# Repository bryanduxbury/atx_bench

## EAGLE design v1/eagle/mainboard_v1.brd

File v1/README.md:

# atx_bench

An digitally-adjustable bench power supply built around an ATX computer power supply.

Check out the DATASHEET for info on features.

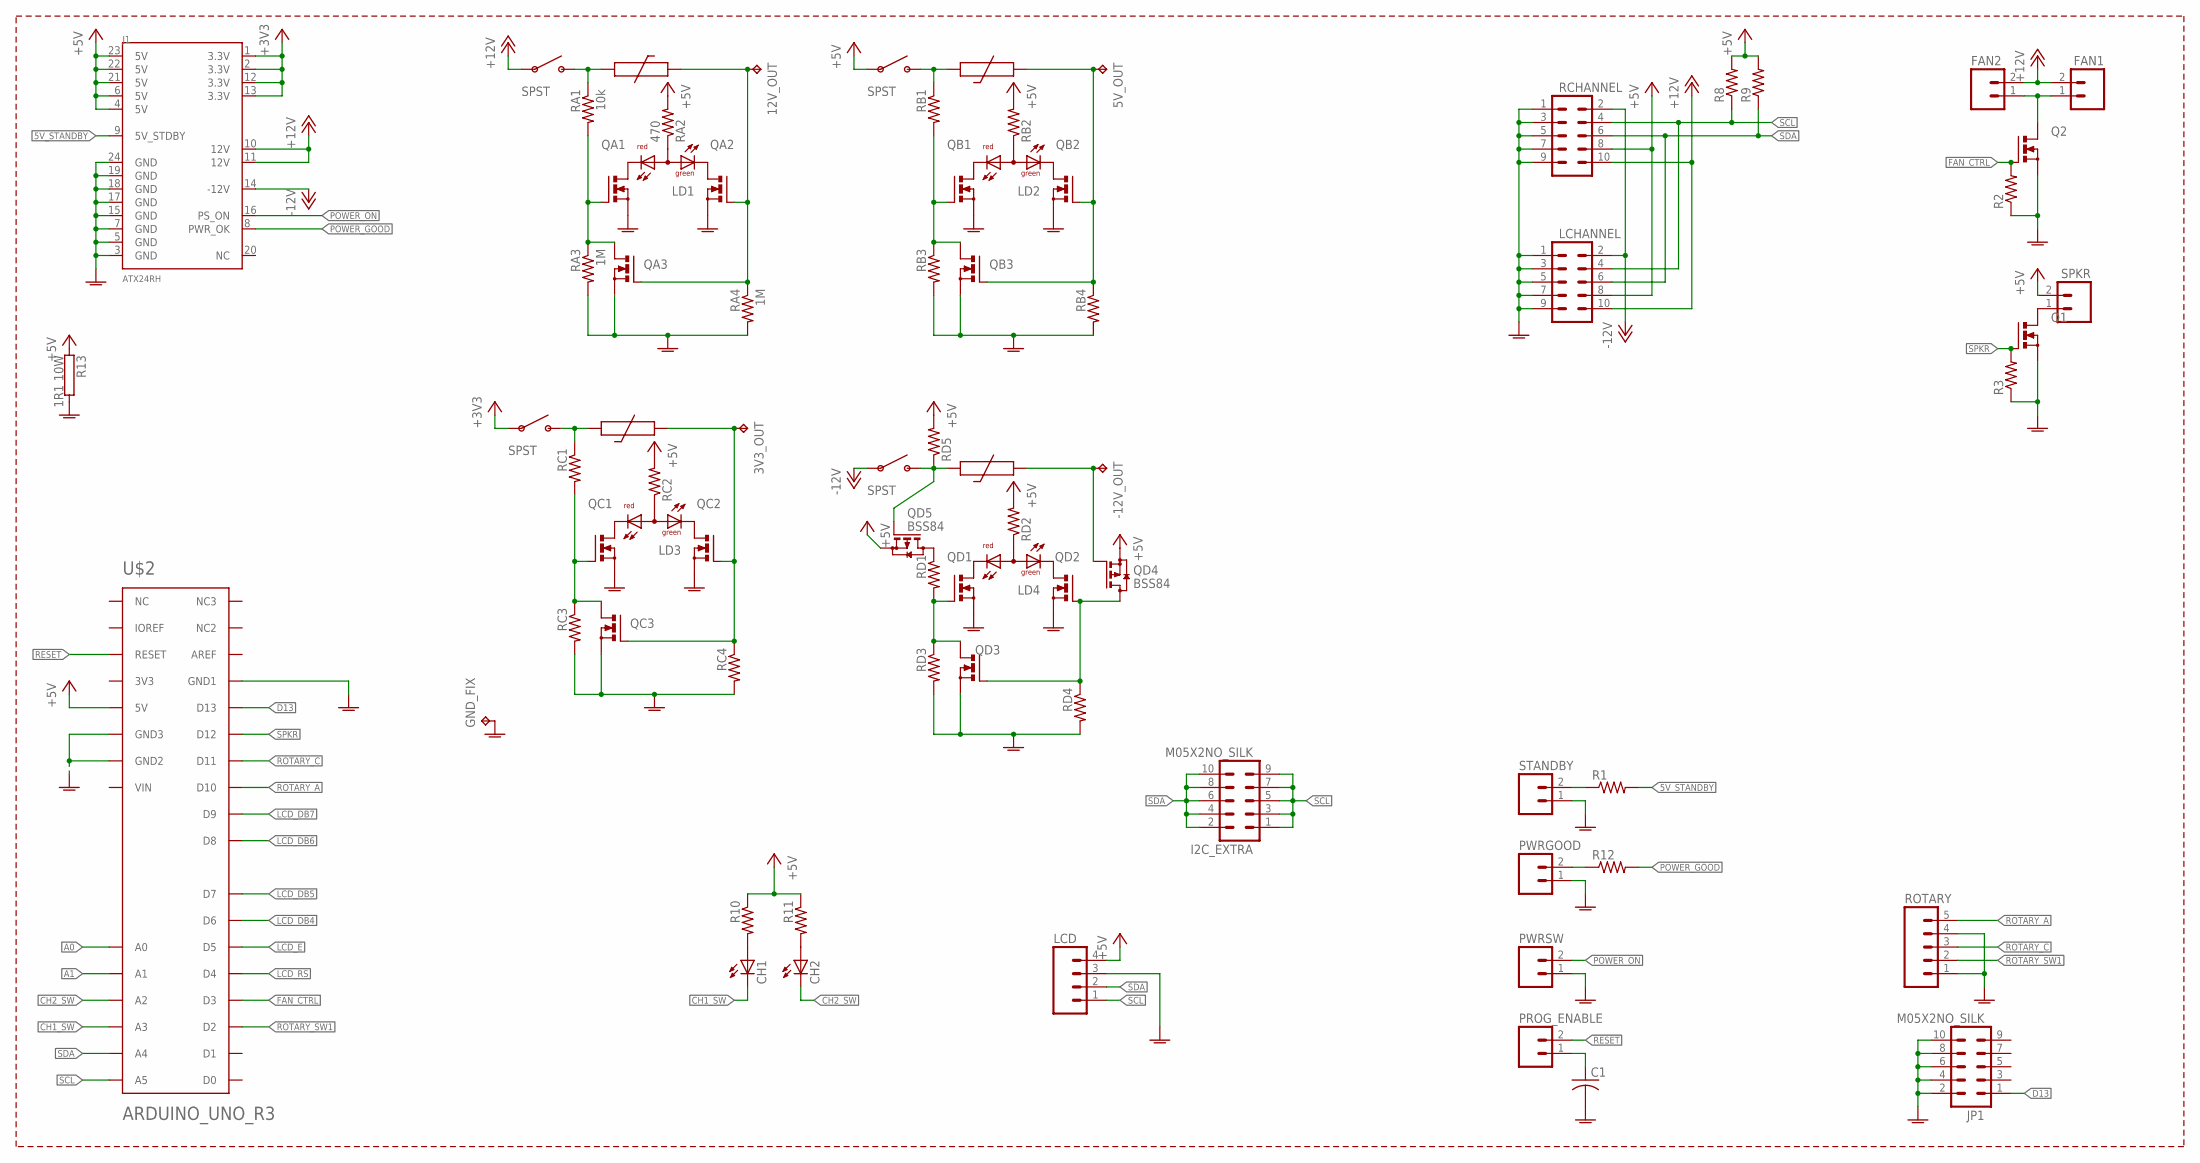
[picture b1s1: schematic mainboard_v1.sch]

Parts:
3V3_OUT, 5V_OUT, 12V_OUT: TPPAD1-20; P1-20
-12V_OUT: TPPAD1-20; P1-20
C1: C-USC0805; C0805
CH1, CH2: LED5MM
FAN1, FAN2: M02PTH; 1X02
GND_FIX: TPPAD1-20; P1-20
I2C_EXTRA: M05X2NO_SILK; 2X5_NOSILK
J1: ATX24RH; ATX24_RIGHT_ANGLE
JP1: M05X2NO_SILK; 2X5_NOSILK
LCD: M04; 04P
LCHANNEL: M05X2SHD; 2X5-SHROUDED
LD1, LD2, LD3, LD4: DUOLED-RG-A; DUOLED-A-5MM
PROG_ENABLE: M02PTH; 1X02
PWRGOOD: M02PTH; 1X02
PWRSW: M02PTH; 1X02
Q1, Q2: 2N7002L; SOT23
QA1, QA2, QA3: 2N7002L; SOT23
QB1, QB2, QB3: 2N7002L; SOT23
QC1, QC2, QC3: 2N7002L; SOT23
QD1, QD2, QD3: 2N7002L; SOT23
QD4, QD5: BSS84; SOT23
R1, R2, R3, R8, R9, R10, R11, R12: R-US_R0805; R0805
R13: 1R1 10W; MNS-5
RA1: 10k; R0805
RA2: 470; R0805
RA3, RA4: 1M; R0805
RB1, RB2, RB3, RB4: R-US_R0805; R0805
RC1, RC2, RC3, RC4: R-US_R0805; R0805
RCHANNEL: M05X2SHD; 2X5-SHROUDED
RD1, RD2, RD3, RD4, RD5: R-US_R0805; R0805
ROTARY: M05; 05P
SPKR: M02PTH; 1X02
STANDBY: M02PTH; 1X02
U$1, U$3, U$4, U$5: MF-R300; MR-300
U$2: ARDUINO_UNO_R3MINIMUM; ARDUINO_UNO_R3_MIN
U$6, U$8, U$9, U$10: SPST; 2P_REMOTE

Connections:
5V_OUT: 5V_OUT.TP, QB2.1 (G), QB3.1 (G), RB4.1, U$3.P$2 (2)
5V_OUT1: 3V3_OUT.TP, QC2.1 (G), QC3.1 (G), RC4.1, U$4.P$2 (2)
5V_STANDBY: J1.9 (5V_STDBY), R1.2
+3V3: J1.1 (3.3V), J1.2 (3.3V), J1.12 (3.3V), J1.13 (3.3V), U$9.1
+5V: J1.4 (5V), J1.6 (5V), J1.21 (5V), J1.22 (5V), J1.23 (5V), LCD.4, LCHANNEL.8, QD4.2 (S), QD5.2 (S), R8.2, R9.2, R10.1, R11.1, R13.1, RA2.2, RB2.2, RC2.2, RCHANNEL.8, RD2.2, RD5.2, SPKR.2, U$2.5V, U$8.1
+12V: FAN1.2, FAN2.2, J1.10 (12V), J1.11 (12V), LCHANNEL.10, RCHANNEL.10, U$6.1
-12V: J1.14 (-12V), LCHANNEL.2, RCHANNEL.2, U$10.1
A0: U$2.A0
A1: U$2.A1
CH1_SW: CH1.K (C), U$2.A3
CH2_SW: CH2.K (C), U$2.A2
D13: JP1.1, U$2.D13
FAN_CTRL: Q2.1 (G), R2.2, U$2.D3
GNDA: C1.2, GND_FIX.TP, J1.3 (GND), J1.5 (GND), J1.7 (GND), J1.15 (GND), J1.17 (GND), J1.18 (GND), J1.19 (GND), J1.24 (GND), JP1.2, JP1.4, JP1.6, JP1.8, JP1.10, LCD.3, LCHANNEL.1, LCHANNEL.3, LCHANNEL.5, LCHANNEL.7, LCHANNEL.9, PWRGOOD.1, PWRSW.1, Q1.2 (S), Q2.2 (S), QA1.2 (S), QA2.2 (S), QA3.2 (S), QB1.2 (S), QB2.2 (S), QB3.2 (S), QC1.2 (S), QC2.2 (S), QC3.2 (S), QD1.2 (S), QD2.2 (S), QD3.2 (S), R2.1, R3.1, R13.2, RA3.2, RA4.2, RB3.2, RB4.2, RC3.2, RC4.2, RCHANNEL.1, RCHANNEL.3, RCHANNEL.5, RCHANNEL.7, RCHANNEL.9, RD3.2, RD4.2, ROTARY.1, ROTARY.4, STANDBY.1, U$2.GND (GND1), U$2.GND2, U$2.GND3
LCD_DB4: U$2.D6
LCD_DB5: U$2.D7
LCD_DB6: U$2.D8
LCD_DB7: U$2.D9
LCD_E: U$2.D5
LCD_RS: U$2.D4
unnamed: FAN1.1, FAN2.1, Q2.3 (D)
unnamed: R1.1, STANDBY.2
unnamed: Q1.3 (D), SPKR.1
unnamed: CH1.A, R10.2
unnamed: CH2.A, R11.2
unnamed: LD2.A, RB2.1
unnamed: LD1.A, RA2.1
unnamed: LD1.CX (CG), QA2.3 (D)
unnamed: LD1.CR, QA1.3 (D)
unnamed: LD2.CX (CG), QB2.3 (D)
unnamed: LD2.CR, QB1.3 (D)
unnamed: PWRGOOD.2, R12.1
unnamed: C1.1, PROG_ENABLE.1
unnamed: RA1.1, U$1.P$2 (2), U$6.2
unnamed: LD3.CR, QC1.3 (D)
unnamed: LD3.A, RC2.1
unnamed: LD3.CX (CG), QC2.3 (D)
unnamed: QD1.1 (G), QD3.3 (D), RD1.2, RD3.1
unnamed: QD5.3 (D), RD1.1
unnamed: LD4.CR, QD1.3 (D)
unnamed: 12V_OUT.TP, QA2.1 (G), QA3.1 (G), RA4.1, U$1.P$1 (1)
unnamed: QB1.1 (G), QB3.3 (D), RB1.2, RB3.1
unnamed: RB1.1, U$3.P$1 (1), U$8.2
unnamed: LD4.A, RD2.1
unnamed: QA1.1 (G), QA3.3 (D), RA1.2, RA3.1
unnamed: LD4.CX (CG), QD2.3 (D)
unnamed: QC1.1 (G), QC3.3 (D), RC1.2, RC3.1
unnamed: RC1.1, U$4.P$1 (1), U$9.2
unnamed: -12V_OUT.TP, QD4.1 (G), U$5.P$2 (2)
unnamed: QD5.1 (G), RD5.1, U$5.P$1 (1), U$10.2
unnamed: QD2.1 (G), QD3.1 (G), QD4.3 (D), RD4.1
POWER_GOOD: J1.8 (PWR_OK), R12.2
POWER_ON: J1.16 (PS_ON), PWRSW.2
RESET: PROG_ENABLE.2, U$2.RESET
ROTARY_A: ROTARY.5, U$2.D10
ROTARY_C: ROTARY.3, U$2.D11
ROTARY_SW1: ROTARY.2, U$2.D2
SCL: I2C_EXTRA.1, I2C_EXTRA.3, I2C_EXTRA.5, I2C_EXTRA.7, I2C_EXTRA.9, LCD.1, LCHANNEL.4, R8.1, RCHANNEL.4, U$2.A5
SDA: I2C_EXTRA.2, I2C_EXTRA.4, I2C_EXTRA.6, I2C_EXTRA.8, I2C_EXTRA.10, LCD.2, LCHANNEL.6, R9.1, RCHANNEL.6, U$2.A4
SPKR: Q1.1 (G), R3.2, U$2.D12

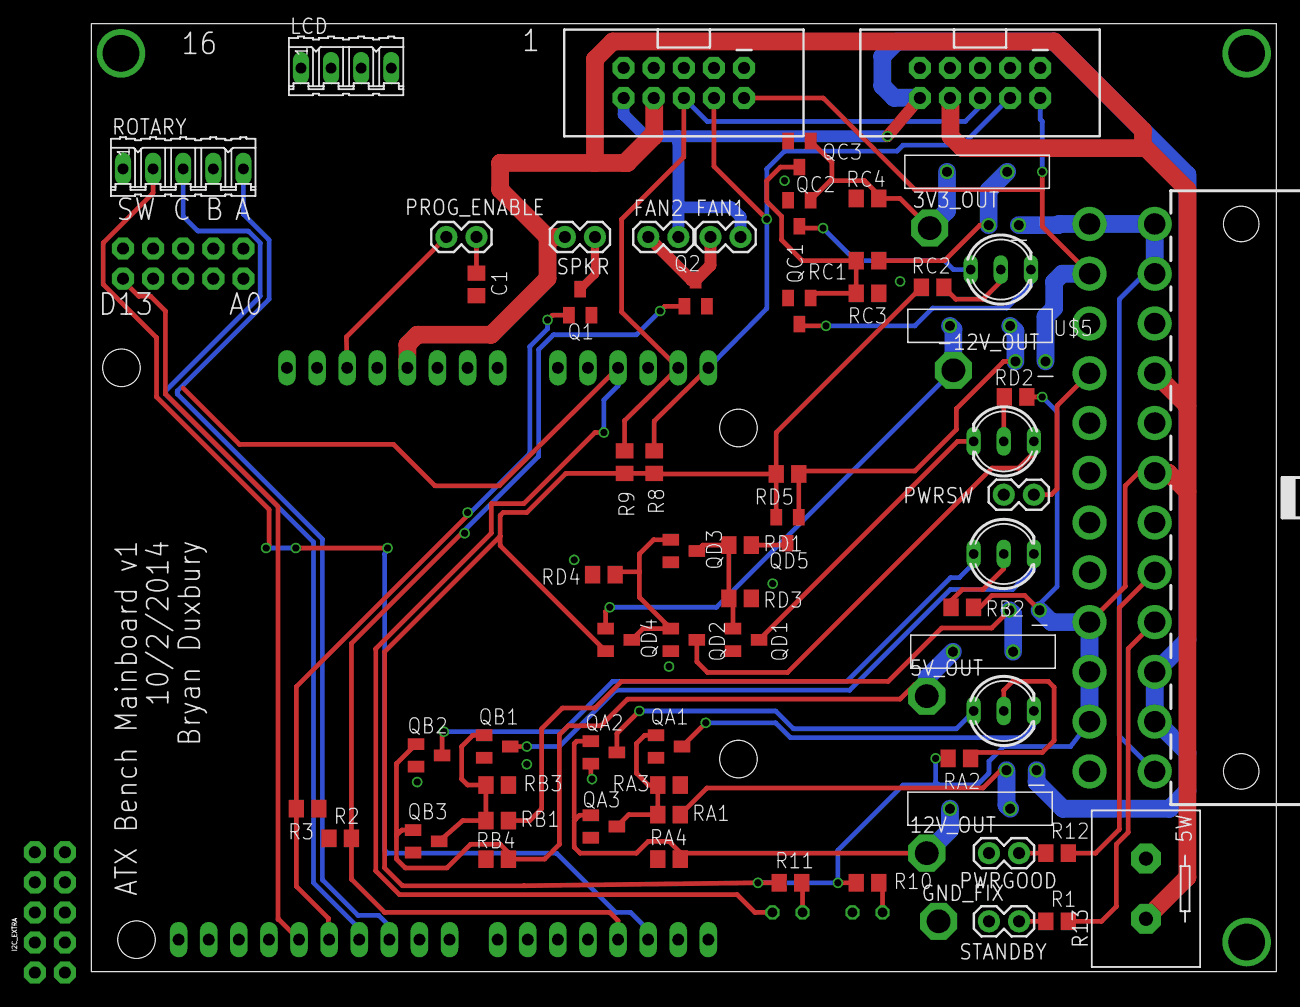
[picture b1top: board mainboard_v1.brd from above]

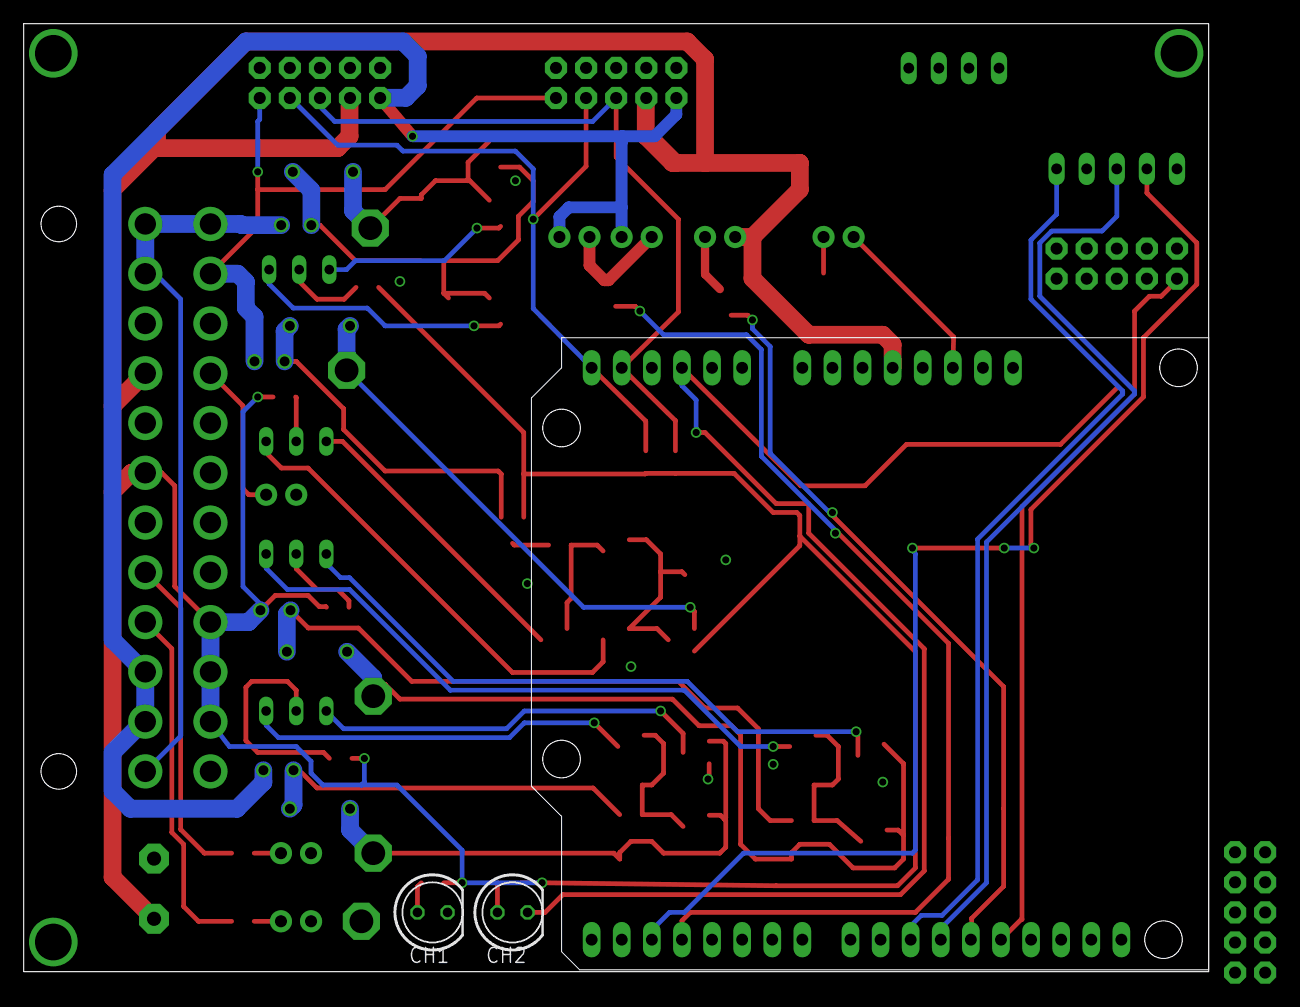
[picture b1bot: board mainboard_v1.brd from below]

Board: 2 copper layers, 100.0 x 80.0 mm, 77 parts (3 on the bottom side), 52 nets.

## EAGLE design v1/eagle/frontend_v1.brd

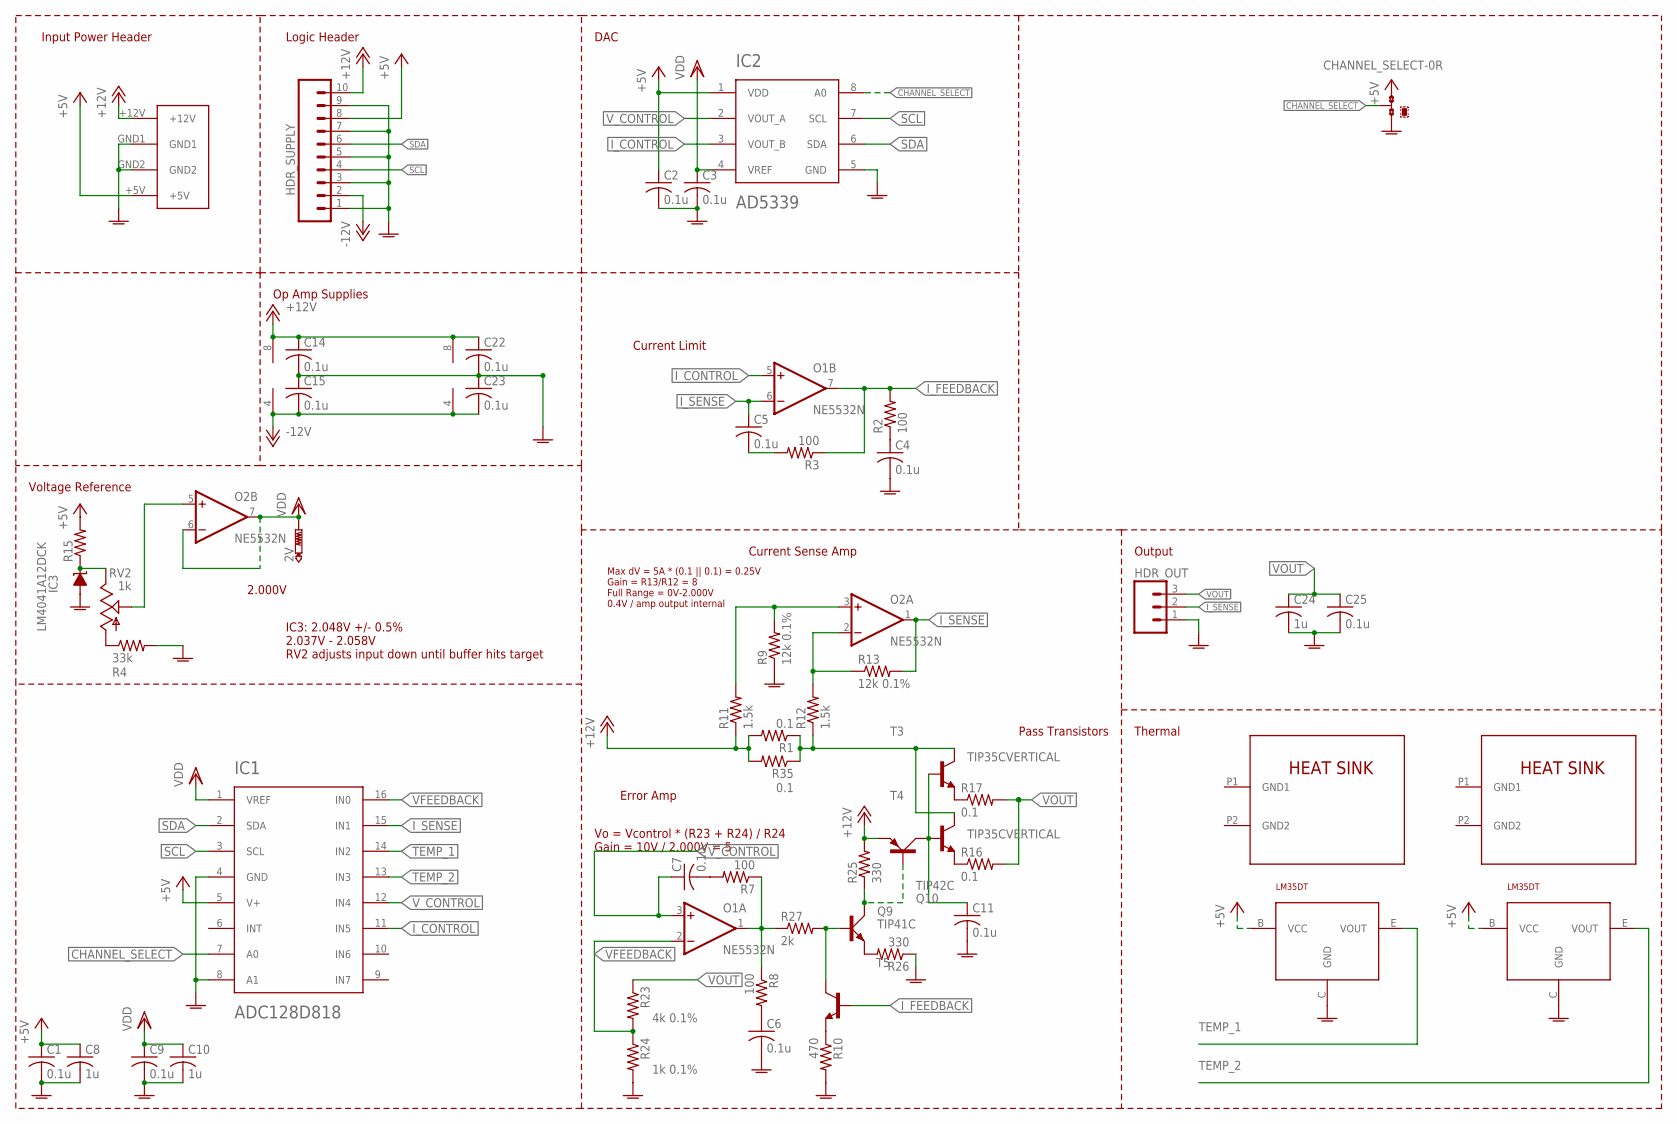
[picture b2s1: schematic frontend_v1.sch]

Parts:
2V: PTR1PAD1-17; P1-17
C1, C2, C3, C4, C5, C6, C7, C9, C11, C14, C15, C22, C23: 0.1u; C0805
C8, C10: 1u; C0805
C24: 1u; C1206
C25: 0.1u; C1206
CHANNEL_SELECT: 0R-JUMPA; A0R-JMP
HDR_OUT: M03; 03P
HDR_SUPPLY: M10; 10P
IC1: ADC128D818; TSSOP16
IC2: AD5339MSOP8; MSOP08
IC3: LM4041A12DCK; DCK_R-PDSO-G5
O1, O2: NE5532N; DIL08
Q9: TIP41C; TO220AV
Q10: TIP42C; TO220AV
R1, R16, R17, R35: 0.1; R2512
R2, R3, R7, R8: 100; M0805
R4: 33k; M0805
R9, R13: 12k 0.1%; M0805
R10: 470; M0805
R11, R12: 1.5k; M0805
R15: R-US_M0805; M0805
R23: 4k 0.1%; M0805
R24: 1k 0.1%; M0805
R25, R26: 330; M0805
R27: 2k; M0805
RV2: 1k; TRIM_POT
T3, T4: TIP35CVERTICAL; TO247
T5: MMBT2222ALT1-NPN-SOT23-BEC; SOT23-BEC
U2, U3: LM35DT; TO220AV
U$1: MOLEX-8981; MOLEX-8981-MALE
U$2, U$3: FA-T220-X

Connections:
+5V: C1.1, C2.1, C8.1, CHANNEL_SELECT.3, HDR_SUPPLY.8, IC1.5 (V+), IC2.1 (VDD), R15.2, U2.B (VCC), U3.B (VCC), U$1.+5V
+12V: C14.1, C22.1, HDR_SUPPLY.10, O1.8 (V+), O2.8 (V+), Q10.E, R1.2, R11.1, R25.2, R35.2, U$1.+12V
-12V: C15.2, C23.2, HDR_SUPPLY.2, O1.4 (V-), O2.4 (V-)
CHANNEL_SELECT: CHANNEL_SELECT.2, IC1.7 (A0), IC2.8 (A0)
GNDA: C1.2, C2.2, C3.2, C4.2, C6.2, C8.2, C9.2, C10.2, C11.2, C14.2, C15.1, C22.2, C23.1, C24.2, C25.2, CHANNEL_SELECT.1, HDR_OUT.1, HDR_SUPPLY.1, HDR_SUPPLY.3, HDR_SUPPLY.5, HDR_SUPPLY.7, HDR_SUPPLY.9, IC1.4 (GND), IC1.8 (A1), IC2.5 (GND), IC3.1 (A), R4.2, R9.1, R10.2, R24.2, R26.1, U2.C (GND), U3.C (GND), U$1.GND1, U$1.GND2
I_CONTROL: IC1.11 (IN5), IC2.3 (VOUT_B), O1.5 (+IN)
I_FEEDBACK: O1.7 (OUT), R2.2, R3.1, T5.B
I_SENSE: C5.1, HDR_OUT.2, IC1.15 (IN1), O1.6 (-IN), O2.1 (OUT), R13.2
unnamed: C4.1, R2.1
unnamed: C5.2, R3.2
unnamed: O2.5 (+IN), RV2.1 (S)
unnamed: R4.1, RV2.3 (A)
unnamed: C6.1, R8.2
unnamed: Q9.B, R27.2, T5.C
unnamed: C7.2, R7.2
unnamed: O2.3 (+IN), R9.2, R11.2
unnamed: O2.2 (-IN), R12.2, R13.1
unnamed: R10.1, T5.E
unnamed: R16.1, T4.P3 (E)
unnamed: R17.1, T3.P3 (E)
unnamed: R1.1, R12.1, R35.1, T3.P2 (C), T4.P2 (C)
unnamed: Q9.C, Q10.B, R25.1
unnamed: Q9.E, R26.2
unnamed: O1.1 (OUT), R7.1, R8.1, R27.1
unnamed: IC3.3 (C), R15.1, RV2.2 (E)
SCL: HDR_SUPPLY.4, IC1.3 (SCL), IC2.7 (SCL)
SDA: HDR_SUPPLY.6, IC1.2 (SDA), IC2.6 (SDA)
TEMP_1: IC1.14 (IN2), U2.E (VOUT)
TEMP_2: IC1.13 (IN3), U3.E (VOUT)
VDD: 2V.TP, C3.1, C9.1, C10.1, IC1.1 (VREF), IC2.4 (VREF), O2.6 (-IN), O2.7 (OUT)
VFEEDBACK: IC1.16 (IN0), O1.2 (-IN), R23.2, R24.1
VOUT: C24.1, C25.1, HDR_OUT.3, R16.2, R17.2, R23.1
VREF: C11.1, Q10.C, T3.P1 (B), T4.P1 (B)
V_CONTROL: C7.1, IC1.12 (IN4), IC2.2 (VOUT_A), O1.3 (+IN)

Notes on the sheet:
Logic Header
Voltage Reference
Op Amp Supplies
Current Sense Amp
Error Amp
Pass Transistors
Current Limit
Output
Input Power Header
2.000V
Thermal
Max dV = 5A * (0.1 || 0.1) = 0.25V Gain = R13/R12 = 8 Full Range = 0V-2.000V 0.4V / amp output internal
IC3: 2.048V +/- 0.5% 2.037V - 2.058V RV2 adjusts input down until buffer hits target
Vo = Vcontrol * (R23 + R24) / R24 Gain = 10V / 2.000V = 5
DAC

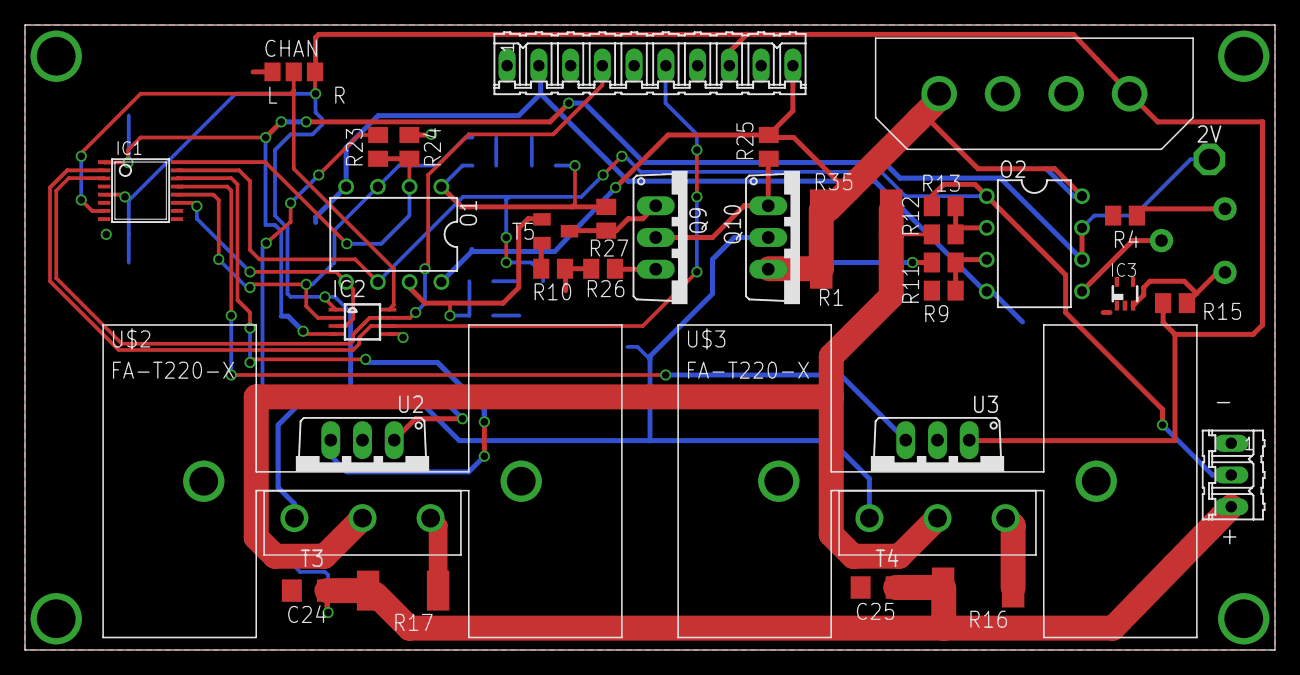
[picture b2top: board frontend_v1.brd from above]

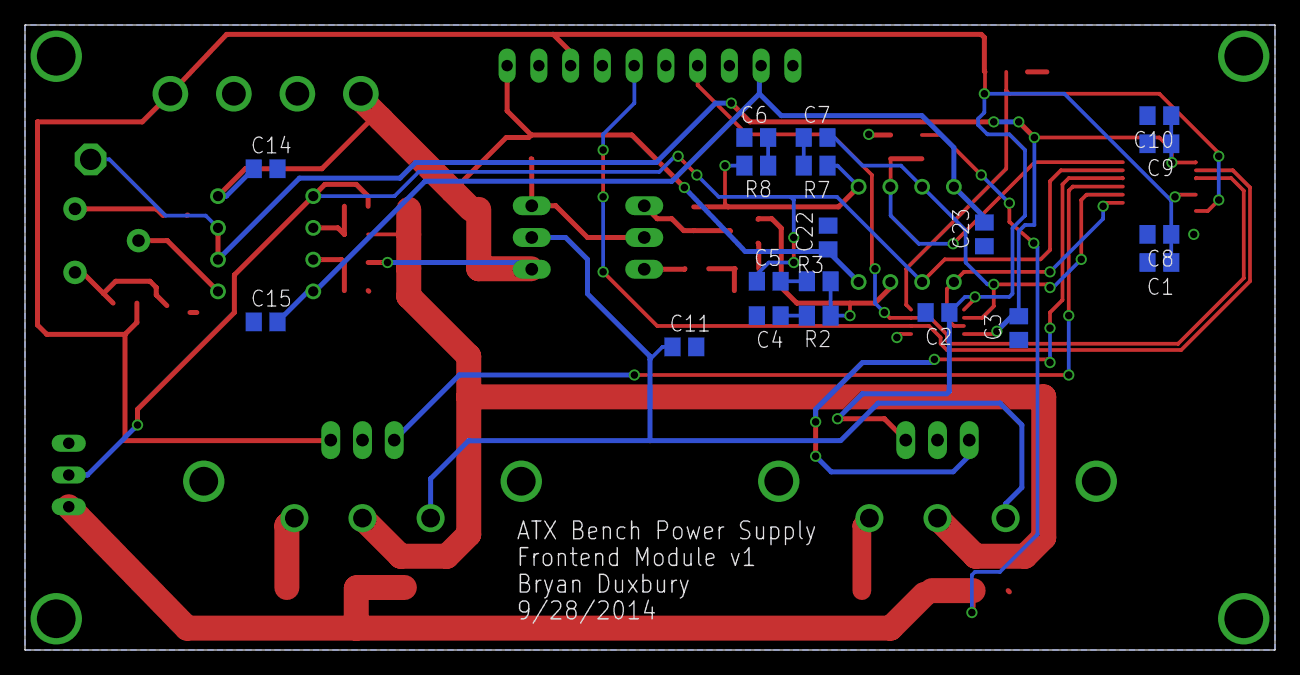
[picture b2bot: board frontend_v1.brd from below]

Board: 2 copper layers, 100.0 x 50.0 mm, 57 parts (19 on the bottom side), 34 nets.

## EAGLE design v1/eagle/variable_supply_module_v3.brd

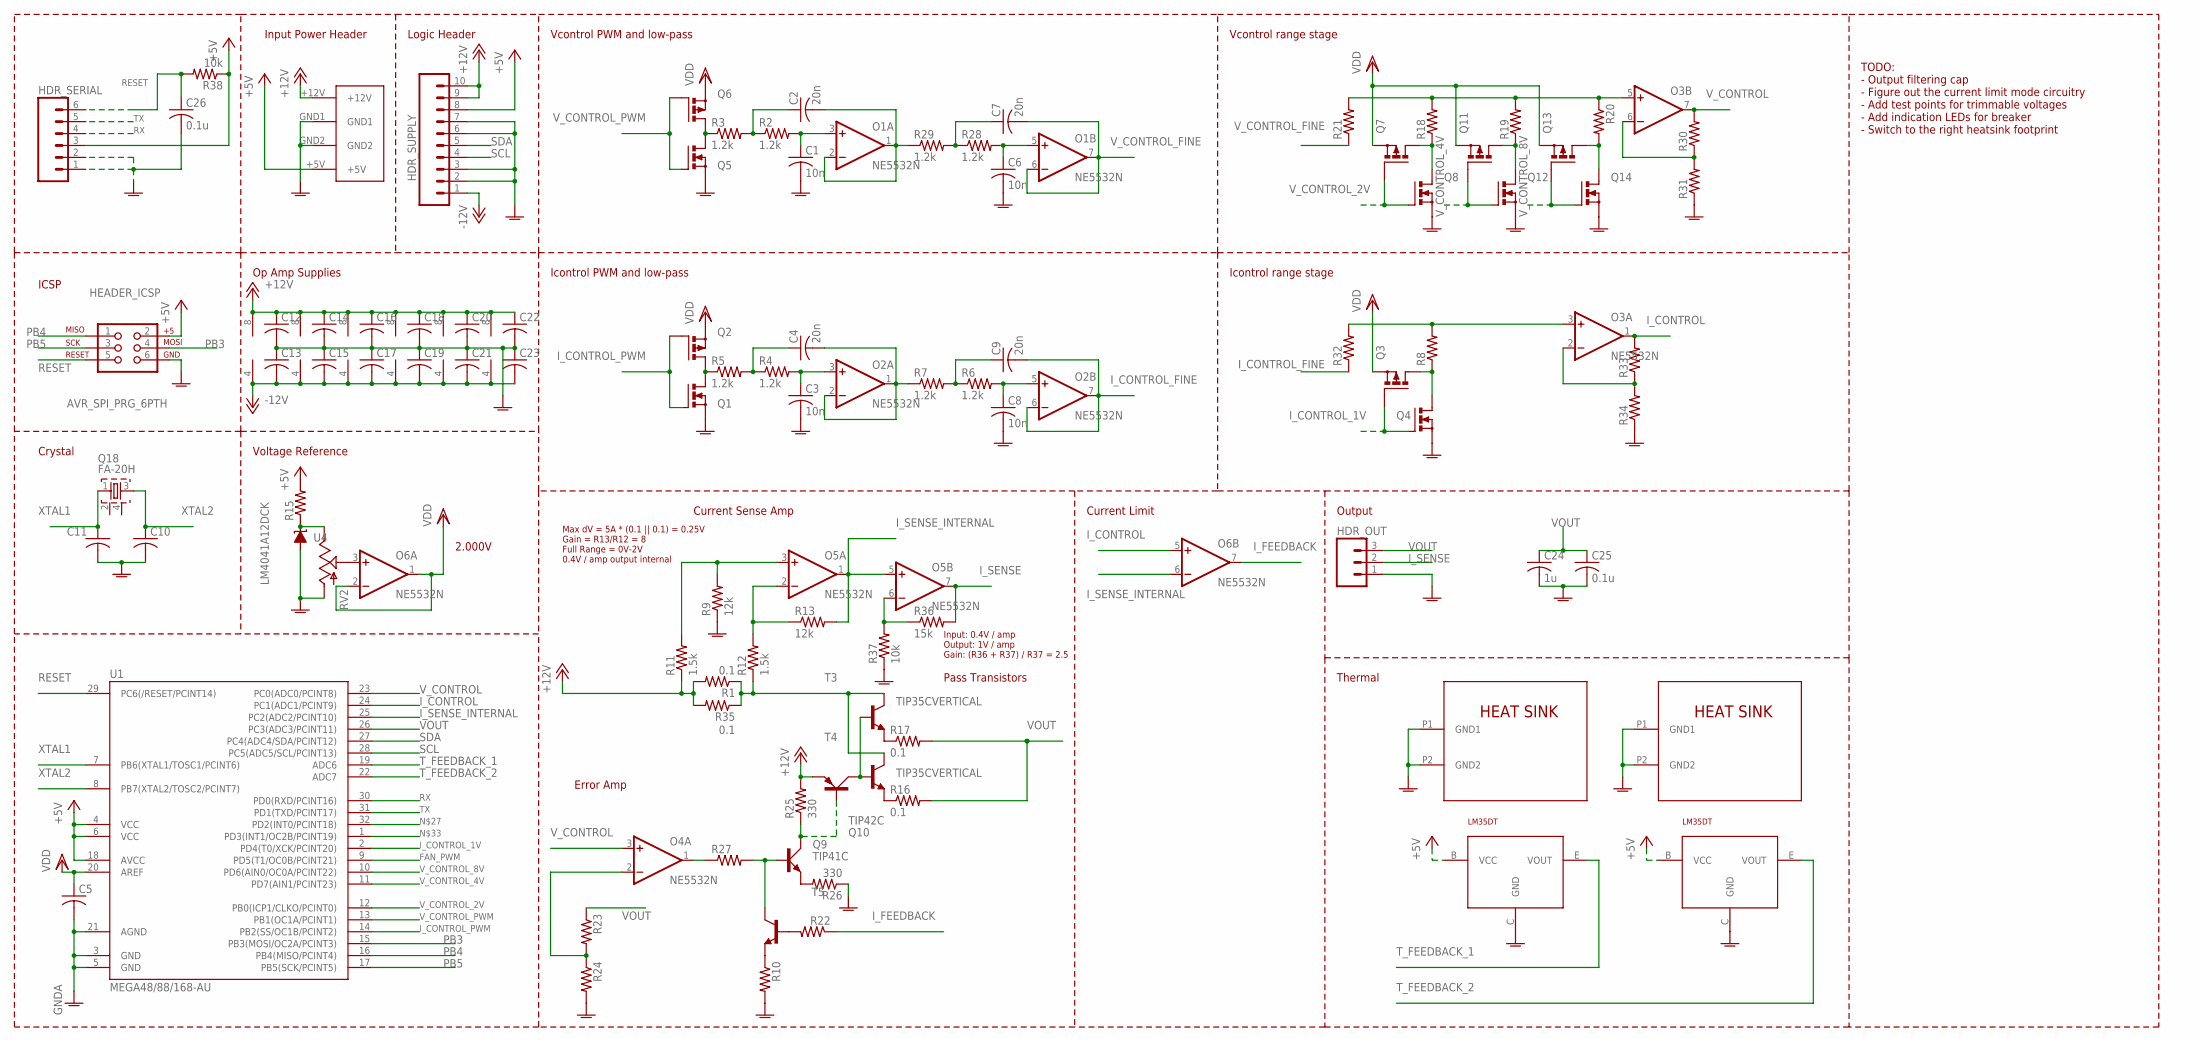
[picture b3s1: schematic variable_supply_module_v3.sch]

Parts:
C1, C3, C6, C8: 10n; C0805
C2, C4, C7, C9: 20n; C0805
C5, C10, C11, C12, C13, C14, C15, C16, C17, C18, C19, C20, C21, C22, C23: C-USC0805; C0805
C24: 1u; C1206
C25: 0.1u; C1206
C26: 0.1u; C0805
HDR_OUT: M03; 03P
HDR_SERIAL: M06LONGPADS; 1X06_LONGPADS
HDR_SUPPLY: M10; 10P
HEADER_ICSP: AVR_SPI_PRG_6PTH; 2X3
O1, O2, O3, O4, O5, O6: NE5532N; DIL08
Q1, Q4, Q5, Q8, Q12, Q14: PMOSFET_NSOT23-GSD; SOT23
Q2, Q3, Q6, Q7, Q11, Q13: PMOSFET_PSOT-23GSD; SOT23
Q9: TIP41C; TO220AV
Q10: TIP42C; TO220AV
Q18: FA-20H
R1, R16, R17, R35: 0.1; R2010
R2, R3, R4, R5, R6, R7, R28, R29: 1.2k; M0805
R8, R10, R15, R18, R19, R20, R21, R22, R23, R24, R27, R30, R31, R32, R33, R34: R-US_M0805; M0805
R9, R13: 12k; M0805
R11, R12: 1.5k; M0805
R25, R26: 330; M0805
R36: 15k; M0805
R37, R38: 10k; M0805
RV2: POTTRIM; TRIM_POT
T3, T4: TIP35CVERTICAL; TO247
T5: MMBT2222ALT1-NPN-SOT23-BEC; SOT23-BEC
U1: MEGA48/88/168-AU; TQFP32-08
U2, U3: LM35DT; TO220AV
U4: LM4041A12DCK; DCK_R-PDSO-G5
U$1: MOLEX-8981; MOLEX-8981-MALE
U$2, U$3: FA-T220-X

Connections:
+5V: HDR_SERIAL.3, HDR_SUPPLY.8, HEADER_ICSP.2, R15.2, R38.1, U1.4 (VCC), U1.6 (VCC), U1.18 (AVCC), U2.B (VCC), U3.B (VCC), U$1.+5V
+12V: C12.1, C14.1, C16.1, C18.1, C20.1, C22.1, HDR_SUPPLY.9, HDR_SUPPLY.10, O1.8 (V+), O2.8 (V+), O3.8 (V+), O4.8 (V+), O5.8 (V+), O6.8 (V+), Q10.E, R1.2, R11.1, R25.2, R35.2, U$1.+12V
-12V: C13.2, C15.2, C17.2, C19.2, C21.2, C23.2, HDR_SUPPLY.1, O1.4 (V-), O2.4 (V-), O3.4 (V-), O4.4 (V-), O5.4 (V-), O6.4 (V-)
FAN_PWM: U1.9 (PD5(T1/OC0B/PCINT21))
FINE_ADJ: C2.2, O1.1 (OUT), O1.2 (-IN), R29.1
FINE_ADJ1: C4.2, O2.1 (OUT), O2.2 (-IN), R7.1
GNDA: C1.2, C3.2, C5.2, C6.2, C8.2, C10.2, C11.2, C12.2, C13.1, C14.2, C15.1, C16.2, C17.1, C18.2, C19.1, C20.2, C21.1, C22.2, C23.1, C24.2, C25.2, C26.2, HDR_OUT.1, HDR_SERIAL.1, HDR_SERIAL.2, HDR_SUPPLY.2, HDR_SUPPLY.3, HDR_SUPPLY.6, HDR_SUPPLY.7, HEADER_ICSP.6, Q1.2 (S), Q4.2 (S), Q5.2 (S), Q8.2 (S), Q12.2 (S), Q14.2 (S), R9.1, R10.2, R24.2, R26.1, R31.1, R34.1, R37.1, RV2.3 (A), U1.3 (GND), U1.5 (GND), U1.21 (AGND), U2.C (GND), U3.C (GND), U4.1 (A), U$1.GND1, U$1.GND2, U$2.P1 (GND1), U$2.P2 (GND2), U$3.P1 (GND1), U$3.P2 (GND2)
I_CONTROL: O3.1 (OUT), O6.5 (+IN), R33.2, U1.24 (PC1(ADC1/PCINT9))
I_CONTROL_1V: Q3.1 (G), Q4.1 (G), U1.2 (PD4(T0/XCK/PCINT20))
I_CONTROL_FINE: C9.2, O2.6 (-IN), O2.7 (OUT), R32.1
I_CONTROL_PWM: Q1.1 (G), Q2.1 (G), U1.14 (PB2(SS/OC1B/PCINT2))
I_FEEDBACK: O6.7 (OUT), R22.1
I_SENSE: HDR_OUT.2, O5.7 (OUT), R36.2
I_SENSE_INTERNAL: O5.1 (OUT), O5.5 (+IN), O6.6 (-IN), R13.2, U1.25 (PC2(ADC2/PCINT10))
unnamed: C1.1, O1.3 (+IN), R2.2
unnamed: C2.1, R2.1, R3.2
unnamed: C3.1, O2.3 (+IN), R4.2
unnamed: C4.1, R4.1, R5.2
unnamed: Q5.3 (D), Q6.3 (D), R3.1
unnamed: Q9.B, R27.2, T5.C
unnamed: Q1.3 (D), Q2.3 (D), R5.1
unnamed: C8.1, O2.5 (+IN), R6.2
unnamed: C9.1, R6.1, R7.2
unnamed: Q13.3 (D), Q14.3 (D), R20.2
unnamed: Q11.3 (D), Q12.3 (D), R19.1
unnamed: Q7.3 (D), Q8.3 (D), R18.1
unnamed: O6.3 (+IN), RV2.1 (S)
unnamed: O3.3 (+IN), R8.2, R32.2
unnamed: O5.3 (+IN), R9.2, R11.2
unnamed: O5.2 (-IN), R12.2, R13.1
unnamed: R10.1, T5.E
unnamed: R16.1, T4.P3 (E)
unnamed: R17.1, T3.P3 (E)
unnamed: R1.1, R12.1, R35.1, T3.P2 (C), T4.P2 (C)
unnamed: O3.2 (-IN), R33.1, R34.2
unnamed: R22.2, T5.B
unnamed: O5.6 (-IN), R36.1, R37.2
unnamed: O3.5 (+IN), R18.2, R19.2, R20.1, R21.2
unnamed: C6.1, O1.5 (+IN), R28.2
unnamed: O4.2 (-IN), R23.2, R24.1
unnamed: Q9.C, Q10.B, R25.1
unnamed: Q9.E, R26.2
unnamed: O4.1 (OUT), R27.1
unnamed: R15.1, RV2.2 (E), U4.3 (C)
unnamed: C7.1, R28.1, R29.2
unnamed: Q3.3 (D), Q4.3 (D), R8.1
unnamed: O3.6 (-IN), R30.1, R31.2
PB3: HEADER_ICSP.4, U1.15 (PB3(MOSI/OC2A/PCINT3))
PB4: HEADER_ICSP.1, U1.16 (PB4(MISO/PCINT4))
PB5: HEADER_ICSP.3, U1.17 (PB5(SCK/PCINT5))
RESET: C26.1, HDR_SERIAL.6, HEADER_ICSP.5, R38.2, U1.29 (PC6(/RESET/PCINT14))
RX: HDR_SERIAL.4, U1.30 (PD0(RXD/PCINT16))
SCL: HDR_SUPPLY.4, U1.28 (PC5(ADC5/SCL/PCINT13))
SDA: HDR_SUPPLY.5, U1.27 (PC4(ADC4/SDA/PCINT12))
TX: HDR_SERIAL.5, U1.31 (PD1(TXD/PCINT17))
T_FEEDBACK_1: U1.19 (ADC6), U2.E (VOUT)
T_FEEDBACK_2: U1.22 (ADC7), U3.E (VOUT)
VDD: C5.1, O6.1 (OUT), O6.2 (-IN), Q2.2 (S), Q3.2 (S), Q6.2 (S), Q7.2 (S), Q11.2 (S), Q13.2 (S), U1.20 (AREF)
VOUT: C24.1, C25.1, HDR_OUT.3, R16.2, R17.2, R23.1, U1.26 (PC3(ADC3/PCINT11))
VREF: Q10.C, T3.P1 (B), T4.P1 (B)
V_CONTROL: O3.7 (OUT), O4.3 (+IN), R30.2, U1.23 (PC0(ADC0/PCINT8))
V_CONTROL_2V: Q7.1 (G), Q8.1 (G), U1.12 (PB0(ICP1/CLKO/PCINT0))
V_CONTROL_4V: Q11.1 (G), Q12.1 (G), U1.11 (PD7(AIN1/PCINT23))
V_CONTROL_8V: Q13.1 (G), Q14.1 (G), U1.10 (PD6(AIN0/OC0A/PCINT22))
V_CONTROL_FINE: C7.2, O1.6 (-IN), O1.7 (OUT), R21.1
V_CONTROL_PWM: Q5.1 (G), Q6.1 (G), U1.13 (PB1(OC1A/PCINT1))
XTAL1: C11.1, Q18.1, U1.7 (PB6(XTAL1/TOSC1/PCINT6))
XTAL2: C10.1, Q18.3, U1.8 (PB7(XTAL2/TOSC2/PCINT7))

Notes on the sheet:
Logic Header
ICSP
Crystal
Voltage Reference
Vcontrol PWM and low-pass
Icontrol PWM and low-pass
Vcontrol range stage
Icontrol range stage
Op Amp Supplies
Current Sense Amp
Error Amp
Pass Transistors
Current Limit
Output
Input Power Header
TODO: - Output filtering cap - Figure out the current limit mode circuitry - Add test points for trimmable voltages - Add indication LEDs for breaker - Switch to the right heatsink footprint
2.000V
Thermal
Max dV = 5A * (0.1 || 0.1) = 0.25V Gain = R13/R12 = 8 Full Range = 0V-2V 0.4V / amp output internal
Input: 0.4V / amp Output: 1V / amp Gain: (R36 + R37) / R37 = 2.5

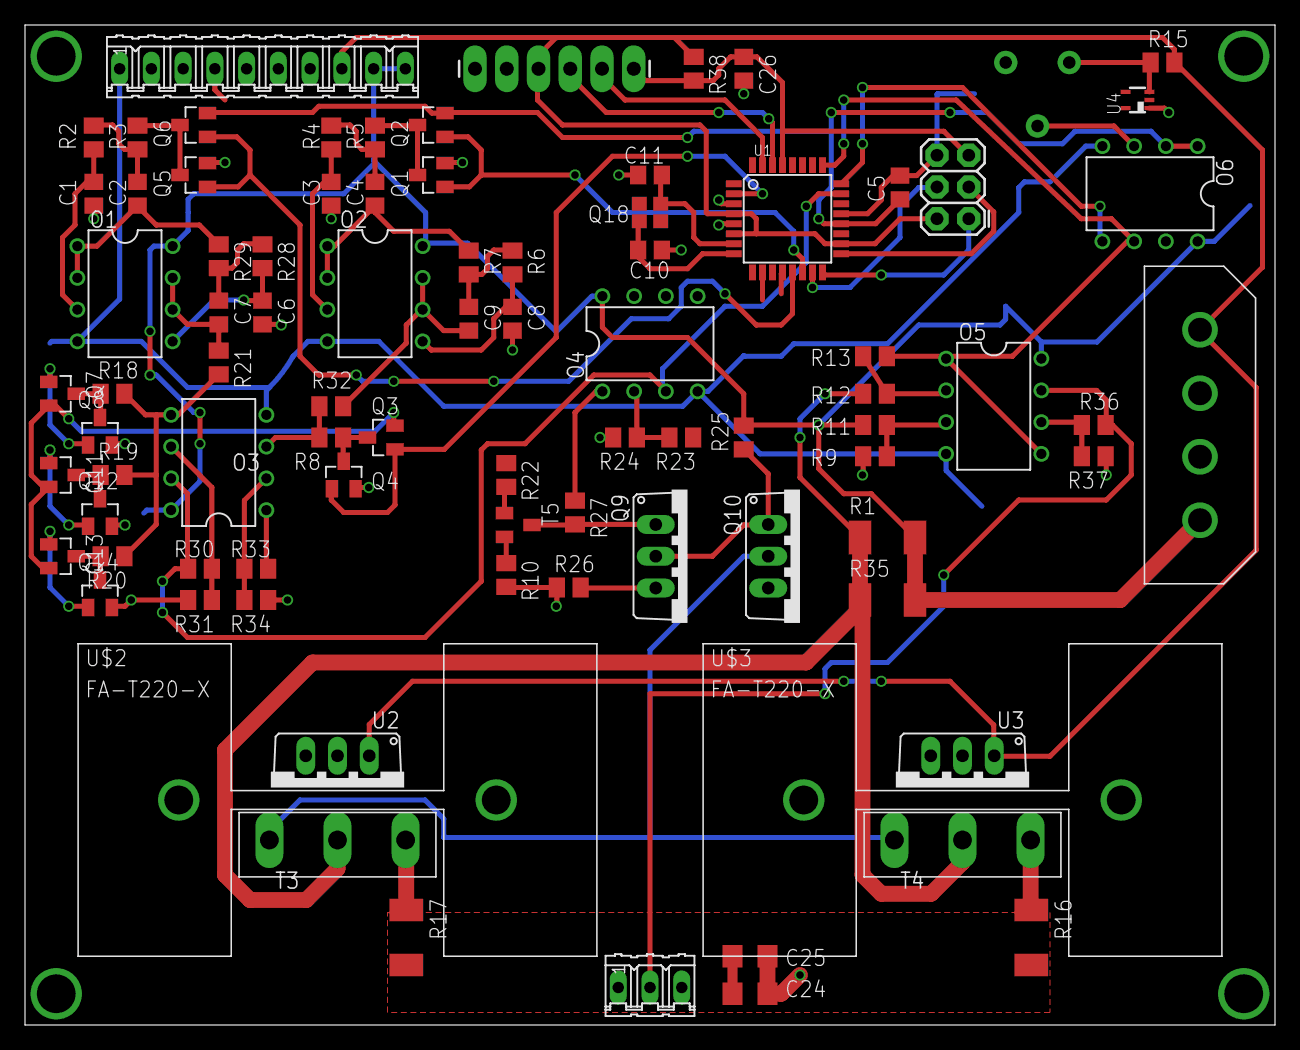
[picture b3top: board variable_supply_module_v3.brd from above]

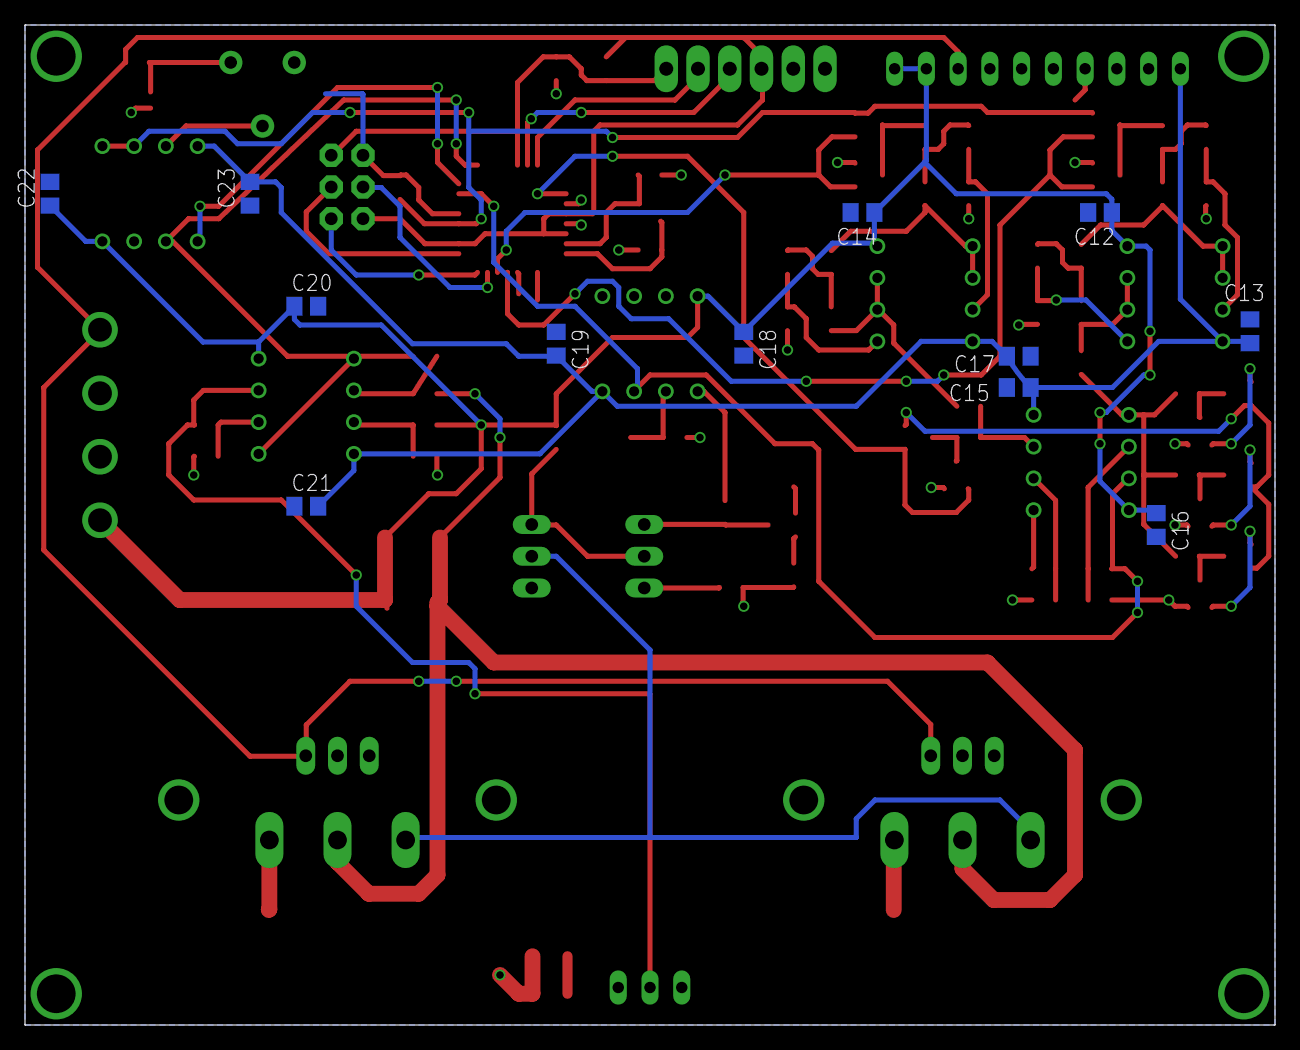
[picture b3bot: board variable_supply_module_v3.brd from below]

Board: 2 copper layers, 100.0 x 80.0 mm, 99 parts (12 on the bottom side), 67 nets.

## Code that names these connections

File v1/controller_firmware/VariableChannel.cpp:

#include "VariableChannel.h"

// DAC channels
#define VCONTROL_DAC 0
#define ICONTROL_DAC 1

// ADC channels
#define VFEEDBACK 0
#define ISENSE 1
#define TEMP_1 2
#define TEMP_2 3
#define VCONTROL_ADC 4
#define ICONTROL_ADC 5

#define LM35_TEMP_CONVERT(MV) ((MV) / 4095 * 2048 / 10)

VariableChannel::VariableChannel(AD533X* dac,
                                  ADC128D818* adc,
                                  uint8_t enableSwitchPin,
                                  uint8_t greenLedPin,
                                  uint8_t redLedPin,
                                  uint8_t voltageCoef,
                                  uint8_t currentCoef) {
  this->dac = dac;
  this->adc = adc;
  this->enable_sw = enableSwitchPin;
  this->green_led = greenLedPin;
  this->red_led = redLedPin;
  this->voltage_coef = voltageCoef;
  this->current_coef = currentCoef;
}

void VariableChannel::begin() {
  // set up the ADC
  adc->setReference(2048);
  adc->setReferenceMode(EXTERNAL_REF);
  adc->setOperationMode(SINGLE_ENDED_WITH_TEMP);
  adc->setConversionMode(CONTINUOUS);
  // all the inputs are in use except IN6
  adc->setDisabledMask(1 << 6);
  adc->begin();

  pinMode(green_led, OUTPUT);
  digitalWrite(green_led, HIGH);
  pinMode(red_led, OUTPUT);
  digitalWrite(red_led, HIGH);

  pinMode(enable_sw, INPUT);
  digitalWrite(enable_sw, HIGH);
}

void VariableChannel::setTargetVoltage(uint16_t target_mv) {
  this->target_mv = target_mv;
}

uint16_t VariableChannel::getTargetVoltage() {
  return target_mv;
}

void VariableChannel::setCurrentLimit(uint16_t limit_ma) {
  this->current_limit_ma = limit_ma;
}

uint16_t VariableChannel::getCurrentLimit() {
  return current_limit_ma;
}

void VariableChannel::setCurrentMode(current_mode_t mode) {
  this->current_mode = mode;
}

current_mode_t VariableChannel::getCurrentMode() {
  return current_mode;
}

uint16_t VariableChannel::getActualVoltage() {
  return last_mv;
}

uint16_t VariableChannel::getActualCurrent() {
  return last_current_ma;
}

int8_t VariableChannel::getAmbientTemp() {
  return last_ambient_degc;
}

int8_t VariableChannel::getPassTemp() {
  return last_pass_degc;
}

bool VariableChannel::isOn() {
  return channel_enabled;
}

void VariableChannel::tick() {
  // determine if the channel is supposed to be enabled
  channel_enabled = digitalRead(enable_sw) == HIGH;

  // read all ADC channels and update caches
  last_mv = adc->read(VFEEDBACK) * voltage_coef;
  last_current_ma = adc->read(ISENSE) * current_coef;
  last_ambient_degc = adc->readTemperatureConverted();
  // average of temperatures of each pass element
  last_pass_degc = LM35_TEMP_CONVERT(adc->read(TEMP_1)) 
                   + LM35_TEMP_CONVERT(adc->read(TEMP_2)) / 2;

  if (channel_enabled) {
    // update DAC with target voltage and current levels
    dac->setOutput(VCONTROL_DAC, target_mv / voltage_coef);
    dac->setOutput(ICONTROL_DAC, current_limit_ma / current_coef);
  } else {
    // update DAC targets to 0
    dac->setOutput(VCONTROL_DAC, 0);
    dac->setOutput(ICONTROL_DAC, 0);
  }
}

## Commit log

2014-05-07 add initial scad work
2014-05-07 eagle work so far
2014-05-09 add skeleton readme and datasheet
2014-05-09 change markdown style in datasheet
2014-05-09 change markdown style in readme
2014-09-28 single-channel frontend ready to be sent out
2014-09-28 very old doodles on a buck/boost style supply frontend
2014-09-28 all sorts of old ideas for how frontend would work
2014-09-28 add gitignore
2014-09-28 used this parts library separately; have since consolidated
2014-09-28 trash unused parts lib
2014-09-28 trash old schematics
2014-09-28 added sketch to experiment with PWM + opamp DAC
2014-09-28 roughing out possible physical configuration
2014-09-29 minor changes
2014-10-03 mainboard is all laid out
2014-10-03 added footprint for arduino
2014-10-03 slight changes for board house
2014-10-04 seems like we've got a decent mockup of the physical layout
2014-10-26 changes to custom part library
2014-10-26 adjustments to reflect newer mainboard design
2014-10-26 sample sketch to experiment with DAC and ADC on frontend board
2015-08-13 outstanding work

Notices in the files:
parts and their libraries:
SparkFun-Electromechanical: Licensing: Creative Commons ShareAlike 4.0 International - https://creativecommons.org/licenses/by-sa/4.0
